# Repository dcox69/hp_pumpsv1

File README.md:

# Pumps & Flowmeters board for HydroPico 1.0

[> Français](#français)

Hydropico is an abandoned project for a hydroponic cultivation control station that I designed and built. It was too complex and too restrictive, so I abandoned the project even though it was almost finished. Here is one of the system's circuit boards, as an example. The images show the V1. 

This board is used to control 5V motors submerged in bottles containing solutions (pH+ and pH-, Plagron A and B), whose tubes are fitted with flow meters and dip into the grow tank. The system regularly monitors and adjusts the solution in the grow tank by injecting one or more products and circulating the solution with a powerful air pump. The entire system is controlled by a script, so I developed a scripting engine using a simple language; here is an example of the code:

```Hydropico scripting language
while (solution.ph > 6.5) {
    pumpfm["PH-"].inject = 4
    relay[8].on
    delay 30
    relay[8].off;
    delay 30
}

if (solution.ec < 2500 && !pumpfm["Plagron A"].error && !pumpfm["Plagron B"].error) {
    // Inject 4 units of Plagron A (pump 3)
    pumpfm["Plagron A"].inject = 4
    // Activate air pump for 15 seconds
    relay[8].on
    delay 15
    relay[8].on;
    // Inject 4 units of Plagron B (pump 4)
    pumpfm["Plagron B"].inject = 4
    // Activate air pump for 15 seconds
    relay[8].on
    delay 15
    relay[8].on;
    // Wait for 30 seconds before checking EC again   
    delay 30
}

every (8 hours) {
    // Activate inside fan
    relay["Inside Fan"].on
    delay 120
    relay["Inside Fan"].off
}
```

I designed this board because I was having EMI issues with the pumps that were causing the I²C bus to crash. The filtering is way too elaborate, but I was fed up with those random crashes that were driving me crazy. The cables from the pumps to the board also have ferrite rings that were specifically chosen for this project.

The KiCad project published here is a V2 that was never built. A much smaller V3 was also in the works when I gave up on the project.

The TVS diodes used on the first PCB were oversized (SMCJ5.0A). For other similar projects, I’ve used SMAJ5.0A diodes, which are more than sufficient. The pumps used in this project draw a maximum of 180 mA.

-----------------------------------------------------------------------------------------------------------------------------

### Français

Hydropico est un projet avorté de station de contrôle de culture hydroponique que j'ai conçu et fabriqué. Trop complexe, trop contraignant, j'ai abandonné le projet alors qu'il était quasiment terminé. Voici, à titre d'exemple, l'une des cartes du système. Les images montrent la V1. 

Cette carte sert à piloter des moteurs 5V immergés dans des flacons contenant des solutions (PH+ et PH-, Plagron A et B), dont les tuyaus sont terminés par un débit-métre, et plongent dans le bac de culture. Le système surveille et ajuste la solution dans le bac de culture régulièrement, en injectant un ou plusieurs produits et en brassant la solution avec une pompe à air puissante. Tout le système est contrôlé par un script, j'ai donc développé un moteur de script avec un langage simple, voici un exemple de code : 

```Hydropico scripting language
while (solution.ph > 6.5) {
    pumpfm["PH-"].inject = 4
    relay[8].on
    delay 30
    relay[8].off;
    delay 30
}

if (solution.ec < 2500 && !pumpfm["Plagron A"].error && !pumpfm["Plagron B"].error) {
    // Inject 4 units of Plagron A (pump 3)
    pumpfm["Plagron A"].inject = 4
    // Activate air pump for 15 seconds
    relay[8].on
    delay 15
    relay[8].on;
    // Inject 4 units of Plagron B (pump 4)
    pumpfm["Plagron B"].inject = 4
    // Activate air pump for 15 seconds
    relay[8].on
    delay 15
    relay[8].onn;
    // Wait for 30 seconds before checking EC again   
    delay 30
}

every (8 hours) {
    // Activate inside fan
    relay["Inside Fan"].on
    delay 120
    relay["Inside Fan"].off
}
```

Cette carte a été mise au point car j'avais des problèmes d'EMI avec les pompes qui faisaient planter le bus I²C. Le filtrage est beaucoup trop élaboré mais j'en avais marre de ces plantages aléatoires qui me rendaient fou. Les câbles des pompes qui vont vers la carte ont en plus des anneaux de ferrites choisis spécifiquement pour le projet. 

Le projet kicad publié ici est une V2 jamais réalisée. Un V3, beaucoup plus petite était aussi en projet au moment ou j'ai abandonné.   

Les TVS utilisées sur le premier PCB étaient surdimensionnées (SMCJ5.0A). Pour d'autres projets similaires, j'ai utilisé des SMAJ5.0A, largement suffisantes. Les pompes utilisées par le projet tirent au maximum 180mA.

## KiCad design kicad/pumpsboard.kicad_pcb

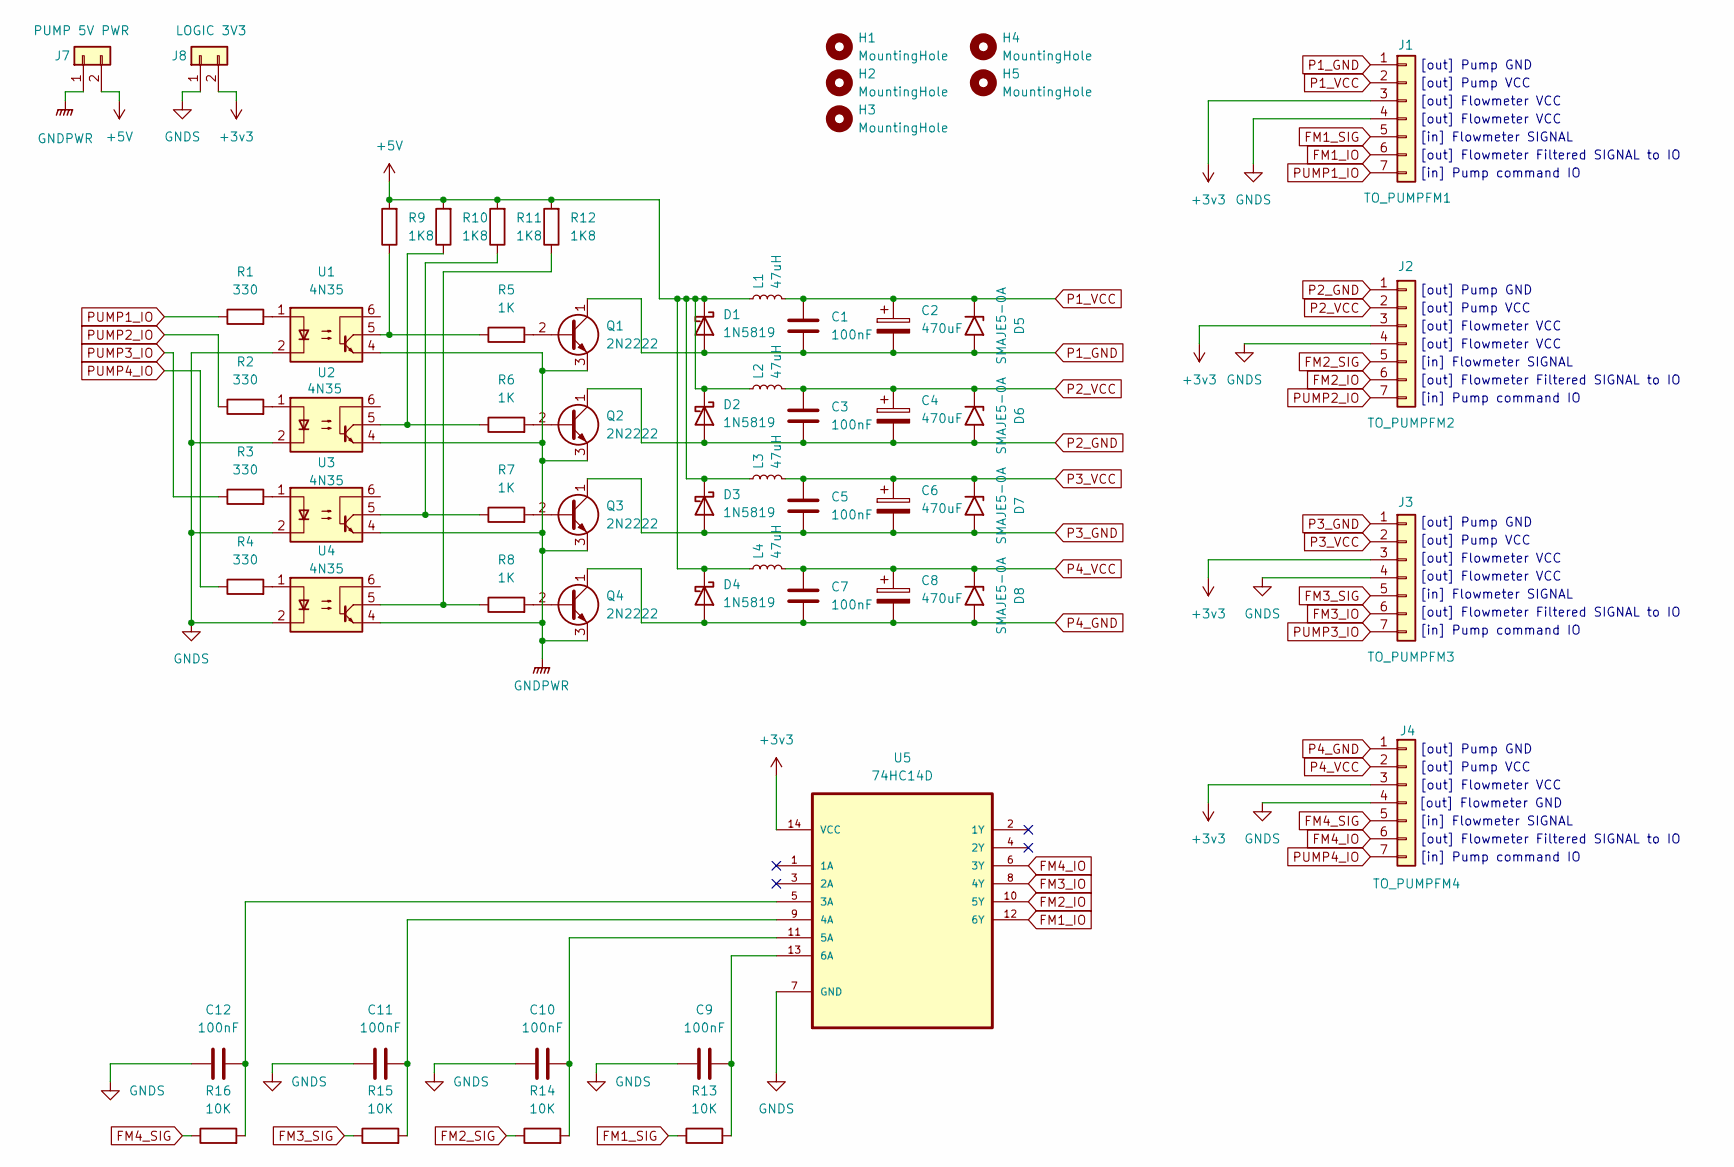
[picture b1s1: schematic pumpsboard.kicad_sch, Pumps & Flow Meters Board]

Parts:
C1, C3, C5, C7: 100nF; Capacitor_THT__C_Rect_L7.0mm_W2.0mm_P5.00mm_07977cdd8c
C2, C4, C6, C8: 470uF; Capacitor_THT__CP_Radial_D10.0mm_P5.00mm_c2050c7ae0
C9, C10, C11, C12: 100nF; Capacitor_SMD__C_1206_3216Metric_Pad1.33x1.80mm_HandSolder_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
D1, D2, D3, D4: 1N5819; Diode_THT__D_DO-41_SOD81_P3.81mm_Vertical_CathodeUp_ca926a0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
D5, D6, D7, D8: SMAJE5-0A; Diode_SMD__D_SMA_d19e0a767d
H1, H2, H3, H4, H5: MountingHole; MountingHole__MountingHole_3.2mm_M3_b9baf9a951
J1: TO_PUMPFM1; Connector_PinHeader_2.00mm__PinHeader_1x07_P2.00mm_Vertical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
J2: TO_PUMPFM2; Connector_PinHeader_2.00mm__PinHeader_1x07_P2.00mm_Vertical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
J3: TO_PUMPFM3; Connector_PinHeader_2.00mm__PinHeader_1x07_P2.00mm_Vertical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
J4: TO_PUMPFM4; Connector_PinHeader_2.00mm__PinHeader_1x07_P2.00mm_Vertical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
J7: PUMP 5V PWR; Connector_JST__JST_XH_B2B-XH-A_1x02_P2.50mm_Vertical_f2470a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
J8: LOGIC 3V3; Connector_JST__JST_XH_B2B-XH-A_1x02_P2.50mm_Vertical_f2470a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
L1, L2, L3, L4: 47uH; dcox69__Inductor_CD54_AE_SMD_76e866a1b3
Q1, Q2, Q3, Q4: 2N2222; Package_TO_SOT_THT__TO-92_Inline_Wide_8b002d4155
R1, R2, R3, R4: 330; Resistor_SMD__R_0805_2012Metric_Pad1.20x1.40mm_HandSolder_5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
R5, R6, R7, R8: 1K; Resistor_SMD__R_0805_2012Metric_Pad1.20x1.40mm_HandSolder_5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
R9, R10, R11, R12: 1K8; Resistor_SMD__R_0805_2012Metric_Pad1.20x1.40mm_HandSolder_5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
R13, R14, R15, R16: 10K; Resistor_SMD__R_0805_2012Metric_Pad1.20x1.40mm_HandSolder_5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
U1, U2, U3, U4: 4N35; Package_DIP__DIP-6_W7.62mm_LongPads_1c3a6a668c
U5: 74HC14D; Package_SO__SO-14_5.3x10.2mm_P1.27mm_938c559d20; MPN 74HC14D

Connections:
+3v3: J1.3, J2.3, J3.3, J4.3, J8.2, U5.14 (VCC)
+5V: D1.1 (K), D2.1 (K), D3.1 (K), D4.1 (K), J7.2, L1.1, L2.1, L3.1, L4.1, R9.2, R10.2, R11.2, R12.2
FM1_IO: J1.6, U5.12 (6Y)
FM1_SIG: J1.5, R13.1
FM2_IO: J2.6, U5.10 (5Y)
FM2_SIG: J2.5, R14.1
FM3_IO: J3.6, U5.8 (4Y)
FM3_SIG: J3.5, R15.1
FM4_IO: J4.6, U5.6 (3Y)
FM4_SIG: J4.5, R16.1
GNDPWR: J7.1, Q1.3 (E), Q2.3 (E), Q3.3 (E), Q4.3 (E), U1.4, U2.4, U3.4, U4.4
GNDS: C9.1, C10.1, C11.1, C12.1, J1.4, J2.4, J3.4, J4.4, J8.1, U1.2, U2.2, U3.2, U4.2, U5.7 (GND)
unnamed: Q1.2 (B), R5.2
unnamed: Q2.2 (B), R6.2
unnamed: Q3.2 (B), R7.2
unnamed: Q4.2 (B), R8.2
unnamed: R1.2, U1.1
unnamed: R2.2, U2.1
unnamed: R3.2, U3.1
unnamed: R4.2, U4.1
unnamed: R5.1, R9.1, U1.5
unnamed: R6.1, R10.1, U2.5
unnamed: R7.1, R11.1, U3.5
unnamed: R8.1, R12.1, U4.5
unnamed: C12.2, R16.2, U5.5 (3A)
unnamed: C11.2, R15.2, U5.9 (4A)
unnamed: C10.2, R14.2, U5.11 (5A)
unnamed: C9.2, R13.2, U5.13 (6A)
P1_GND: C1.2, C2.2, D1.2 (A), D5.2 (A2), J1.1, Q1.1 (C)
P1_VCC: C1.1, C2.1, D5.1 (A1), J1.2, L1.2
P2_GND: C3.2, C4.2, D2.2 (A), D6.2 (A2), J2.1, Q2.1 (C)
P2_VCC: C3.1, C4.1, D6.1 (A1), J2.2, L2.2
P3_GND: C5.2, C6.2, D3.2 (A), D7.2 (A2), J3.1, Q3.1 (C)
P3_VCC: C5.1, C6.1, D7.1 (A1), J3.2, L3.2
P4_GND: C7.2, C8.2, D4.2 (A), D8.2 (A2), J4.1, Q4.1 (C)
P4_VCC: C7.1, C8.1, D8.1 (A1), J4.2, L4.2
PUMP1_IO: J1.7, R1.1
PUMP2_IO: J2.7, R2.1
PUMP3_IO: J3.7, R3.1
PUMP4_IO: J4.7, R4.1

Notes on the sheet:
[out] Pump GND
[out] Flowmeter VCC
[out] Flowmeter GND
[out] Flowmeter Filtered SIGNAL to IO
[out] Pump VCC
[in] Flowmeter SIGNAL
[in] Pump command IO

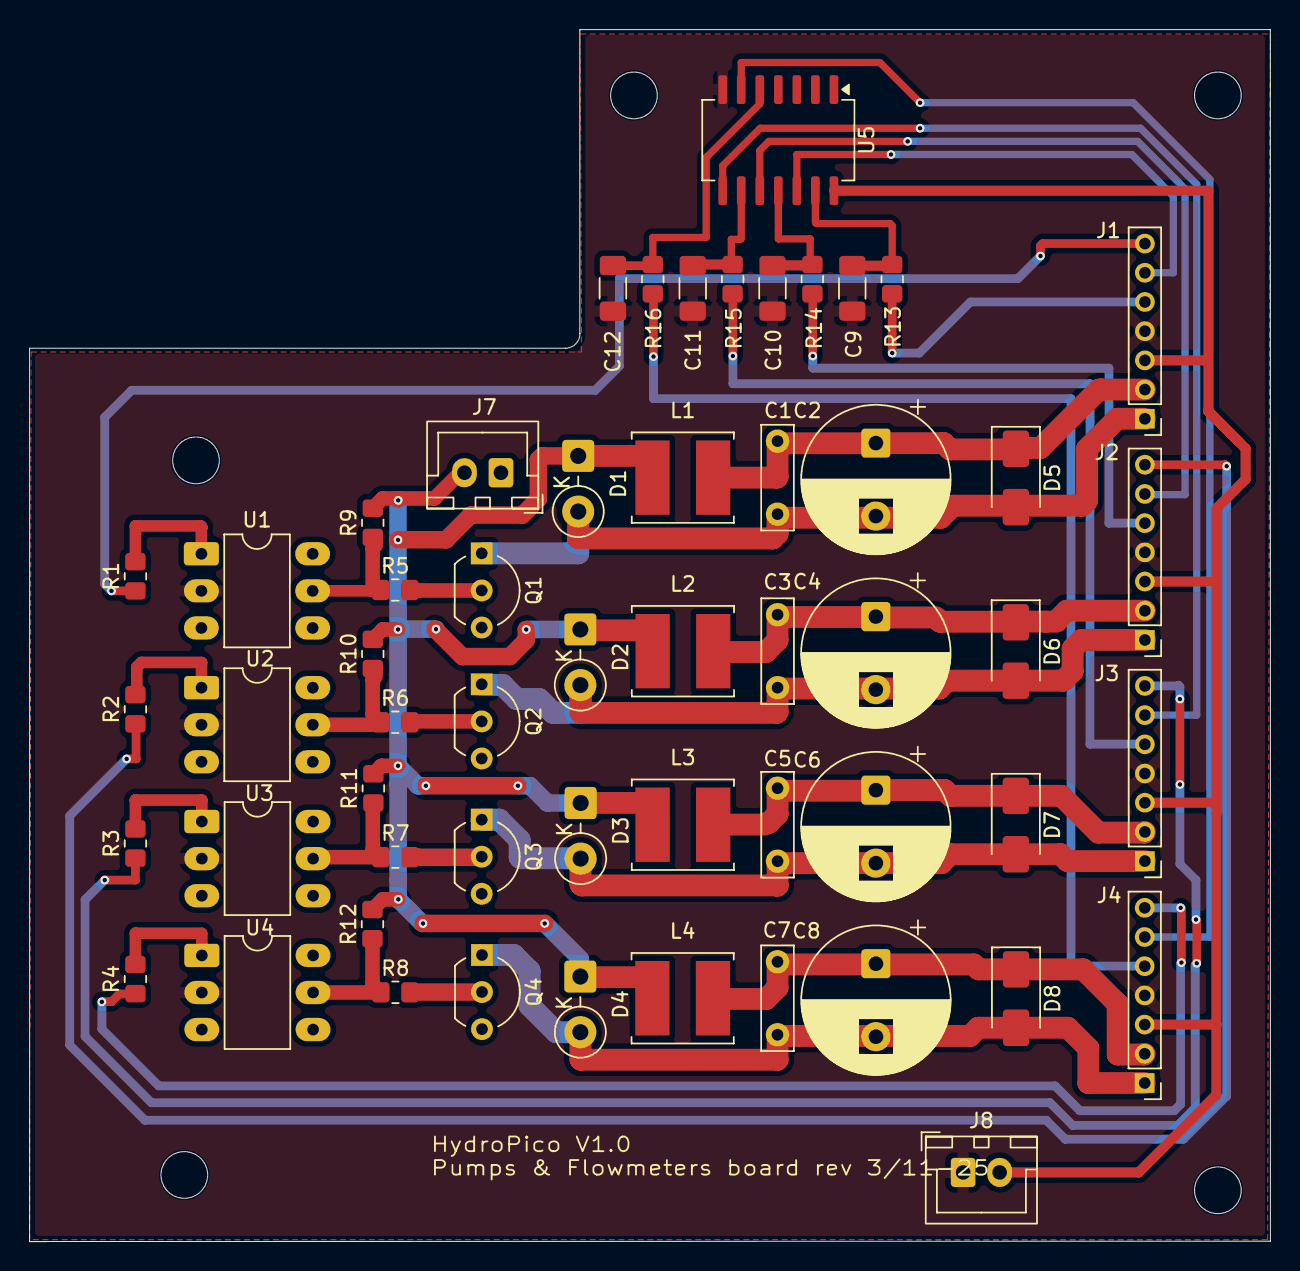
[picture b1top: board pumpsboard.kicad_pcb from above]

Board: 2 copper layers, 85.0 x 83.0 mm, 60 parts (0 on the bottom side), 40 nets.
